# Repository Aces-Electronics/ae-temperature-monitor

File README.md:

# AE Temperature Monitor Firmware
Firmware for the Aces Electronics Temperature Monitor, utilizing ESP-NOW for low-latency communication with the Smart Shunt gateway.

## Features
- **Remote Monitoring**: Measures temperature using a high-accuracy sensor.
- **Battery Powered**: Optimized for low-power operation.
- **Wireless Relay**: Transmits data to the Smart Shunt via ESP-NOW.
- **Auto-Discovery**: Automatically detected and registered by the Smart Shunt and Cloud Dashboard.

## Communication Protocol (ESP-NOW)
The Sensor broadcasts a `struct_message_temp_sensor` payload which is received by the Smart Shunt. The Shunt then relays this data to the Cloud Dashboard for real-time alerts and historical logging.

## Build & Flash
The project uses PlatformIO.
```bash
pio run -t upload
pio run -t upload
```

## OTA Reliability
- **Loop Prevention**: Rejects updates if the version matches the currently installed firmware.
- **JIT Delivery**: Updates are pushed via the Shunt gateway immediately after an uplink.

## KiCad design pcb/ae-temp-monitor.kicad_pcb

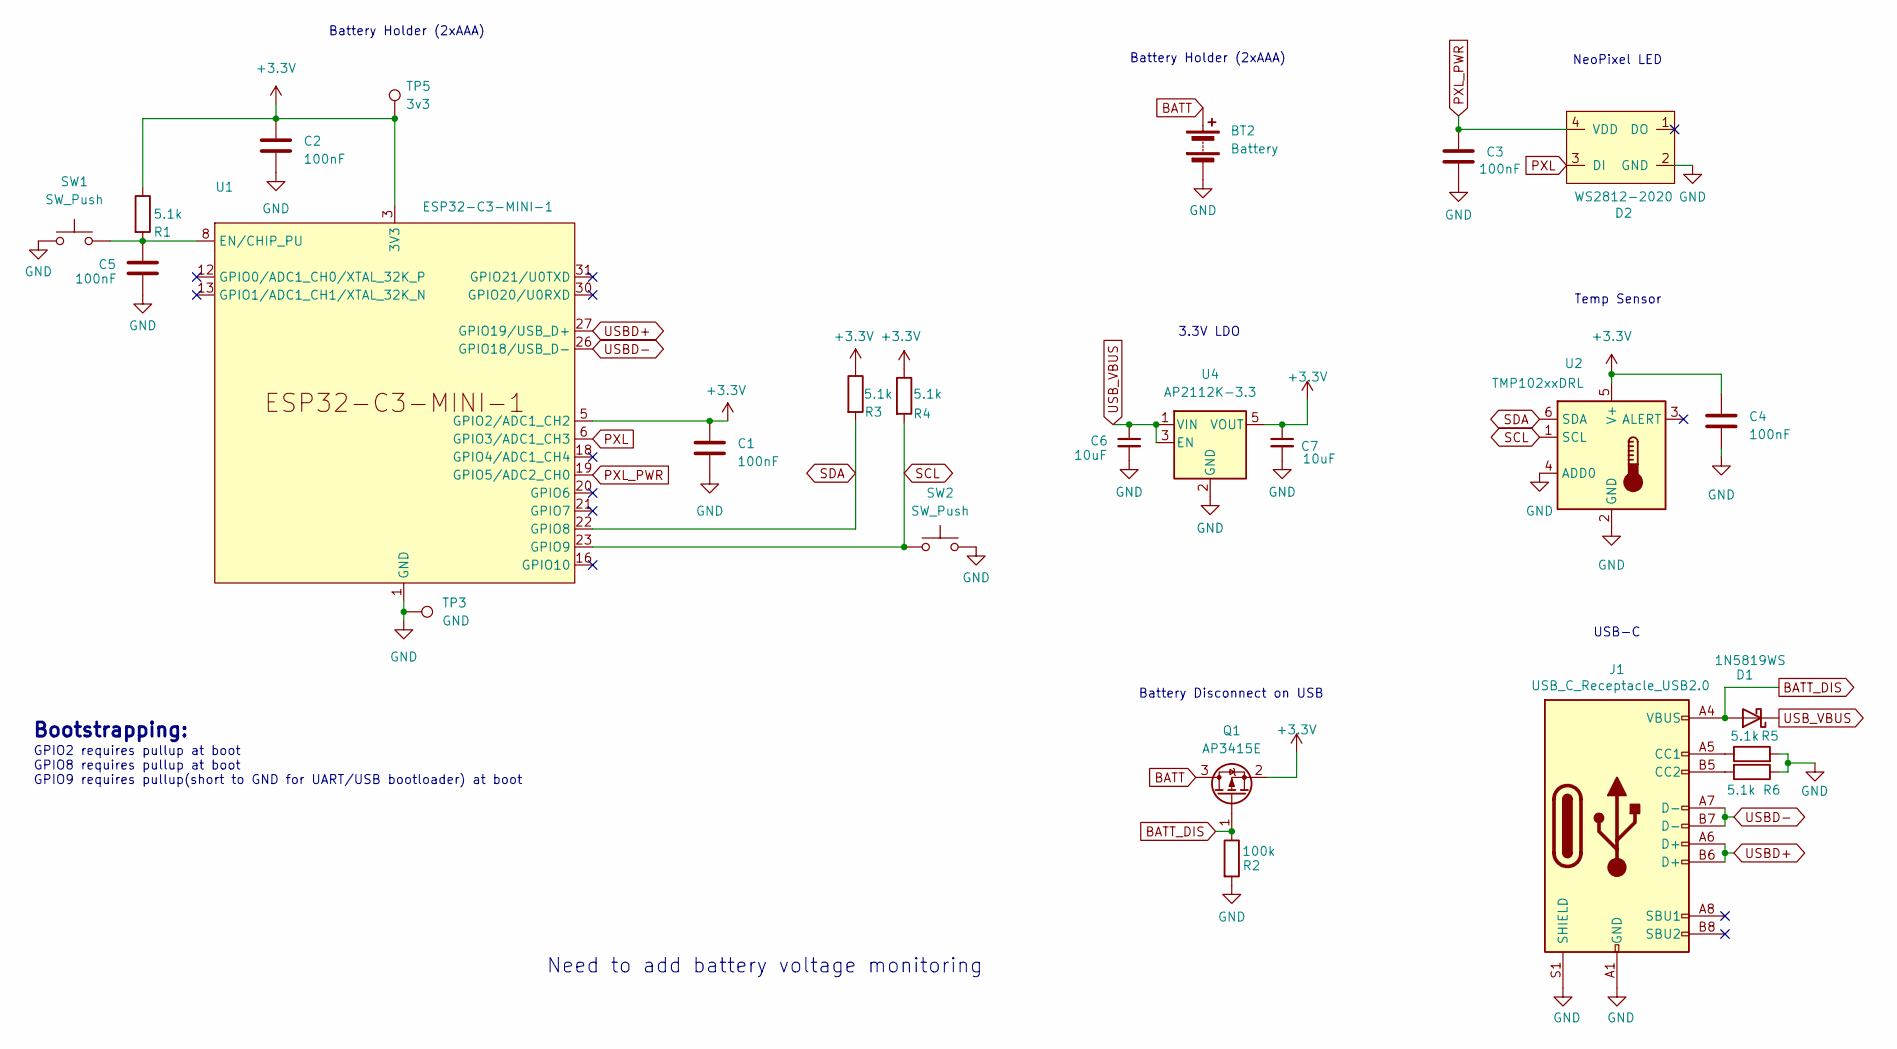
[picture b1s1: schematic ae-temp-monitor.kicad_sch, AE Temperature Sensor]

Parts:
BT2: Battery; BatteryHolder_BH-AAA-B5AK001_C964882; lcsc C964882
C1, C2, C3, C4, C5: 100nF; C_0402_1005Metric; lcsc C1525
C6, C7: 10uF; C_0603_1608Metric; lcsc C19702
D1: 1N5819WS; D_SOD-323; lcsc C191023
D2: WS2812-2020; LED_WS2812B-2020_PLCC4_2.0x2.0mm; lcsc C965555
J1: USB_C_Receptacle_USB2.0; USB_C_Receptacle_GCT_USB4110; lcsc C5187472
Q1: AP3415E; SOT-23; lcsc C2876004
R1, R3, R4, R5, R6: 5.1k; R_0402_1005Metric; lcsc C25905
R2: 100k; R_0402_1005Metric; lcsc C25741
SW1, SW2: SW_Push; ALPSALPINE-SKSCLBE010_C115361; lcsc C115361
TP3: GND; TestPoint_Pad_D1.0mm
TP5: 3v3; TestPoint_Pad_D1.0mm
U1: ESP32-C3-MINI-1; lcsc C5290152
U2: TMP102xxDRL; SOT-563; lcsc C99269
U4: AP2112K-3.3; SOT-23-5; lcsc C51118

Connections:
+3.3V: C1.1, C2.1, C4.1, C7.1, Q1.2 (S), R1.1, R3.1, R4.1, TP5.1, U1.3 (3V3), U1.5 (GPIO2/ADC1_CH2), U2.5 (V+), U4.5 (VOUT)
BATT: BT2.1 (+), Q1.3 (D)
BATT_DIS: D1.2 (A), J1.A4 (VBUS), J1.A9 (VBUS), J1.B4 (VBUS), J1.B9 (VBUS), Q1.1 (G), R2.1
GND: BT2.2 (-), C1.2, C2.2, C3.2, C4.2, C5.2, C6.2, C7.2, D2.2 (GND), J1.A1 (GND), J1.A12 (GND), J1.B1 (GND), J1.B12 (GND), J1.S1 (SHIELD), R2.2, R5.2, R6.1, SW1.2, SW2.2, TP3.1, U1.1 (GND), U1.2 (GND), U1.11 (GND), U1.14 (GND), U1.36 (GND), U1.37 (GND), U1.38 (GND), U1.39 (GND), U1.40 (GND), U1.41 (GND), U1.42 (GND), U1.43 (GND), U1.44 (GND), U1.45 (GND), U1.46 (GND), U1.47 (GND), U1.48 (GND), U1.49 (GND), U1.50 (GND), U1.51 (GND), U1.52 (GND), U1.53 (GND), U2.2 (GND), U2.4 (ADD0), U4.2 (GND)
unnamed: J1.A5 (CC1), R5.1
unnamed: J1.B5 (CC2), R6.2
unnamed: C5.1, R1.2, SW1.1, U1.8 (EN/CHIP_PU)
PXL: D2.3 (DI), U1.6 (GPIO3/ADC1_CH3)
PXL_PWR: C3.1, D2.4 (VDD), U1.19 (GPIO5/ADC2_CH0)
SCL: R4.2, SW2.1, U1.23 (GPIO9), U2.1 (SCL)
SDA: R3.2, U1.22 (GPIO8), U2.6 (SDA)
USBD+: J1.A6 (D+), J1.B6 (D+), U1.27 (GPIO19/USB_D+)
USBD-: J1.A7 (D-), J1.B7 (D-), U1.26 (GPIO18/USB_D-)
USB_VBUS: C6.1, D1.1 (K), U4.1 (VIN), U4.3 (EN)

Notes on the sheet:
Bootstrapping:
Battery Disconnect on USB
Temp Sensor
3.3V LDO
GPIO2 requires pullup at boot GPIO8 requires pullup at boot GPIO9 requires pullup(short to GND for UART/USB bootloader) at boot
NeoPixel LED
Need to add battery voltage monitoring
USB-C
Battery Holder (2xAAA)

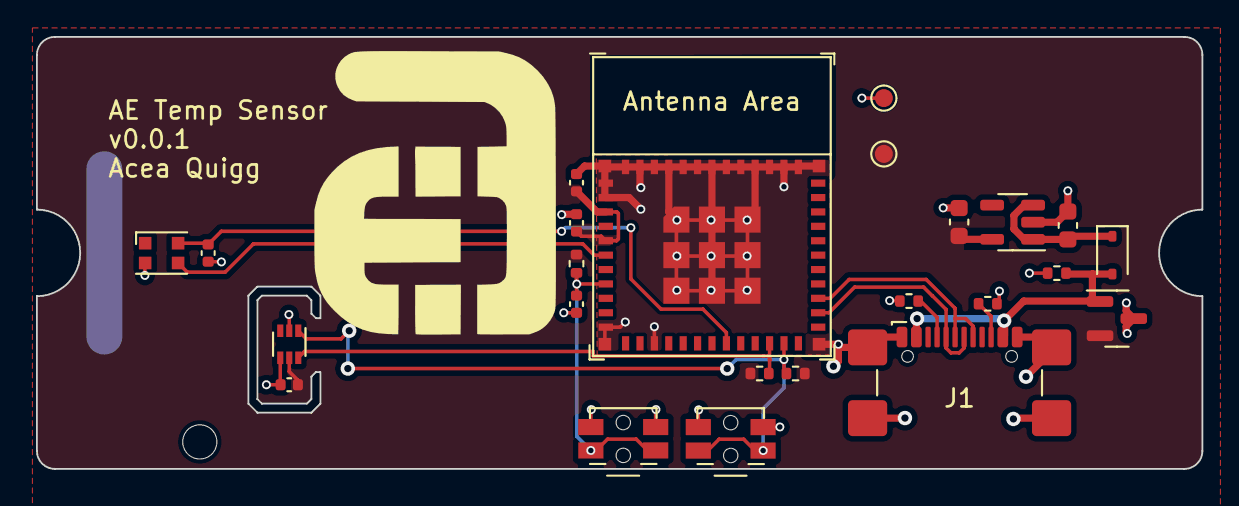
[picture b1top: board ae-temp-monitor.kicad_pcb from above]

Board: 2 copper layers, 64.8 x 24.0 mm, 25 parts (1 on the bottom side), 14 nets.

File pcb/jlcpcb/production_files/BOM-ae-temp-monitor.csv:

Comment,Designator,Footprint,LCSC,Quantity
SW_Push,"SW1,SW2",ALPSALPINE-SKSCLBE010_C115361,C115361,2
100nF,"C1,C2,C3,C4,C5",C_0402_1005Metric,C1525,5
1N5819WS,D1,D_SOD-323,C191023,1
10uF,"C6,C7",C_0603_1608Metric,C19702,2
100k,R2,R_0402_1005Metric,C25741,1
5.1k,"R1,R3,R4,R5,R6",R_0402_1005Metric,C25905,5
ESP32-C3-MINI-1,U1,ESP32-C3-MINI-1,C2838502,1
AP2112K-3.3,U4,SOT-23-5,C51118,1
USB_C_Receptacle_USB2.0,J1,USB_C_Receptacle_GCT_USB4110,C5187472,1
AP3415E,Q1,SOT-23,C5189719,1
Battery,BT2,BatteryHolder_BH-AAA-B5AK001_C964882,C964882,1
WS2812-2020,D2,LED_WS2812B-2020_PLCC4_2.0x2.0mm,C965555,1
TMP102xxDRL,U2,SOT-563,C99269,1

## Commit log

2026-01-06 adding step and proxy
2026-01-25 working
2026-01-27 Implement hardware versioning and build automation
2026-01-27 ota wip
2026-01-27 mesh fixes
2026-01-27 mesh fix
2026-01-30 upding defs
2026-02-01 adding OTA
2026-02-01 ota bug fix
2026-02-01 ota fixes
2026-02-01 ota fix
2026-02-01 updatings defs
2026-02-01 fixing the mesh
2026-02-01 doco update
2026-02-02 updating defs
2026-02-02 loop fix
2026-02-03 updating readmes
2026-02-04 Add GitHub issue templates (bugs/features)
